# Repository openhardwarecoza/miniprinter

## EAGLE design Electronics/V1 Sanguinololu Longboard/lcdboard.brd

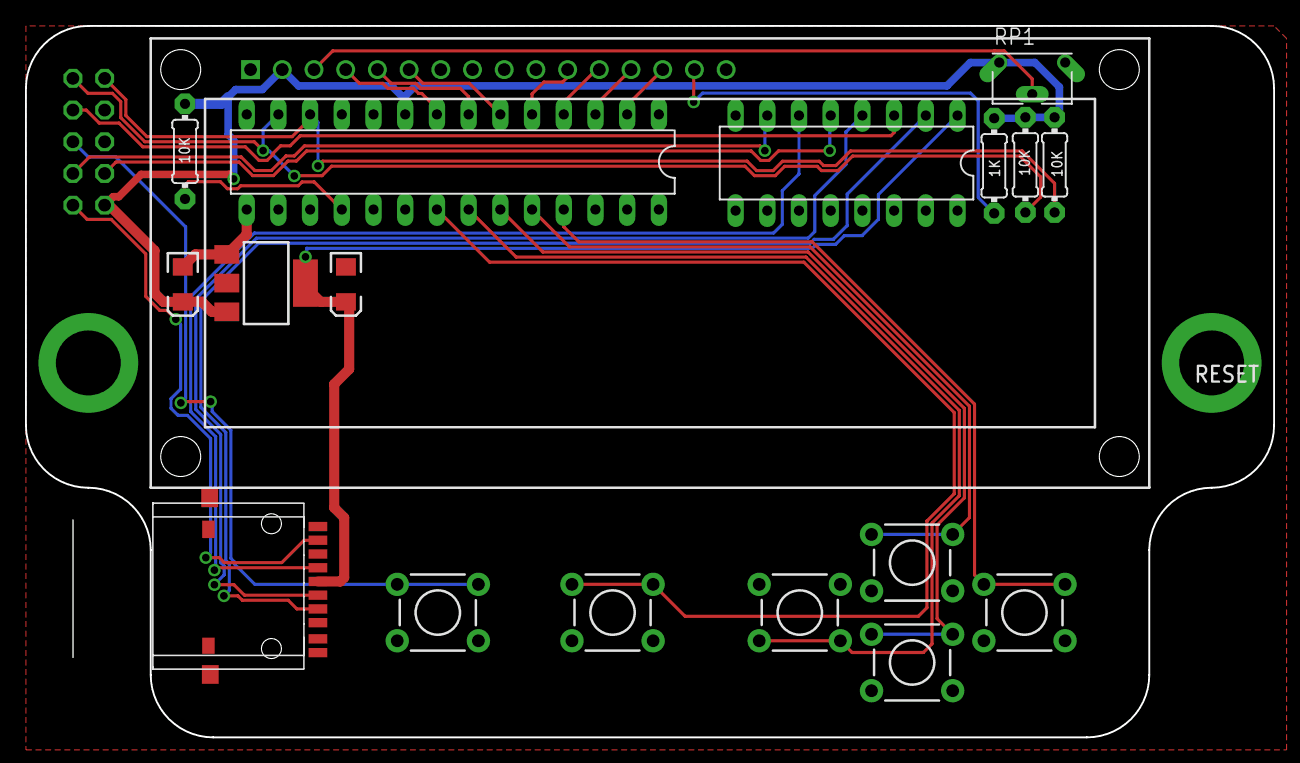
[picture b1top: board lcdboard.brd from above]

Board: 2 copper layers, 100.0 x 57.0 mm, 19 parts (1 on the bottom side), 28 nets.

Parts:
C2, C6: 10uF; EIA3216
IC1: MCP23017SP; DIL28-3
IC3: 1117-33; SOT223
IC5: 4050N; DIL16
JP1: 2X05
LCD16: LCD-HD447804-HOLES16X2-4-HOLES; LCD-16X2-4HOLES
R1, R2, R3, R6: 0204/7
RP1: BOURNS 3362-S-1-103LF; POT_B64W
S1, S2, S3, S4, S5, S6: RESET; TACTILE-PTH
U2: USD-SOCKETUSD; USD-SOCKET-PP

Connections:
3V3SD: C6.A, IC3.4, IC5.1, U2.4
5V: C2.A, IC1.9, IC3.3, JP1.2, LCD16.2, R1.1, R2.2, R3.2, R6.2, RP1.E
CS: IC5.2, U2.2
DB4: IC1.5, LCD16.11
DB5: IC1.4, LCD16.12
DB6: IC1.3, LCD16.13
DB7: IC1.2, LCD16.14
DI: IC5.4, U2.3
DO: JP1.1, U2.7
E: IC1.6, LCD16.6
GND: C2.C, C6.C, IC1.10, IC1.15, IC1.16, IC1.17, IC3.1, IC5.8, JP1.6, LCD16.1, LCD16.16, RP1.A, S1.3, S1.4, S2.3, S2.4, S3.3, S3.4, S4.3, S4.4, S5.3, S5.4, S6.3, S6.4, U2.6, U2.GND1, U2.GND2
MCURESET: JP1.5, S1.1, S1.2
MOSI: IC5.5, JP1.4
unnamed: LCD16.3, RP1.S
unnamed: LCD16.15, R6.1
P1: IC1.25, S2.1, S2.2
P2: IC1.24, S3.1, S3.2
P3: IC1.23, S4.1, S4.2
P4: IC1.22, S5.1, S5.2
P5: IC1.21, S6.1, S6.2
RESET: IC1.18, R3.1
RS: IC1.8, LCD16.4
RW: IC1.7, LCD16.5
SC: IC5.6, U2.5
SCK: IC5.7, JP1.3
SCL: IC1.12, JP1.10, R2.1
SDA: IC1.13, JP1.9, R1.2
SDS: IC5.3, JP1.7

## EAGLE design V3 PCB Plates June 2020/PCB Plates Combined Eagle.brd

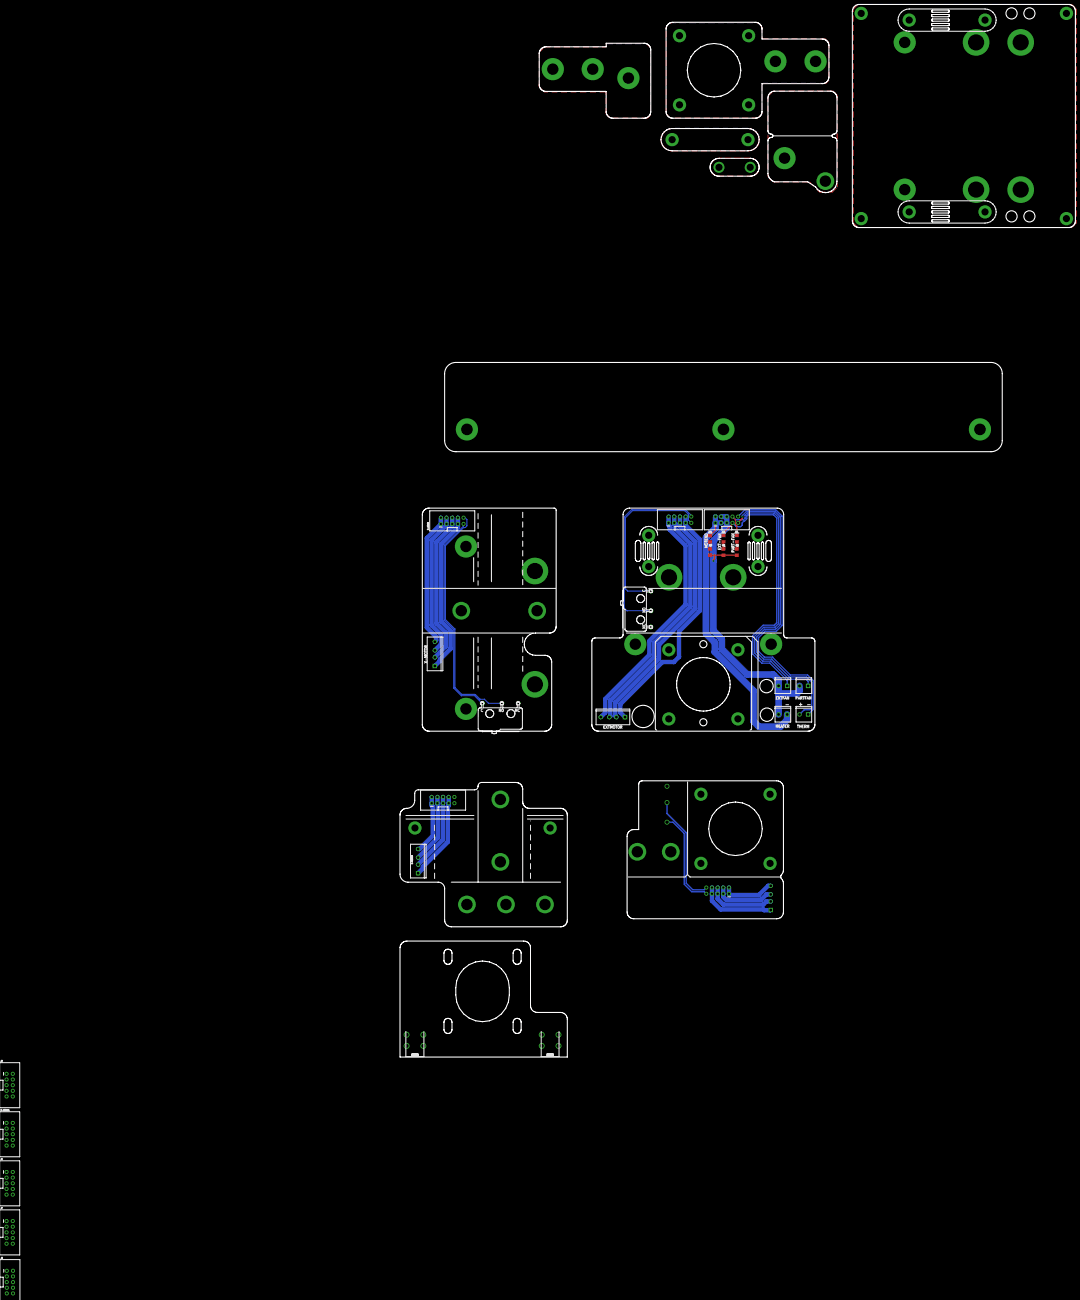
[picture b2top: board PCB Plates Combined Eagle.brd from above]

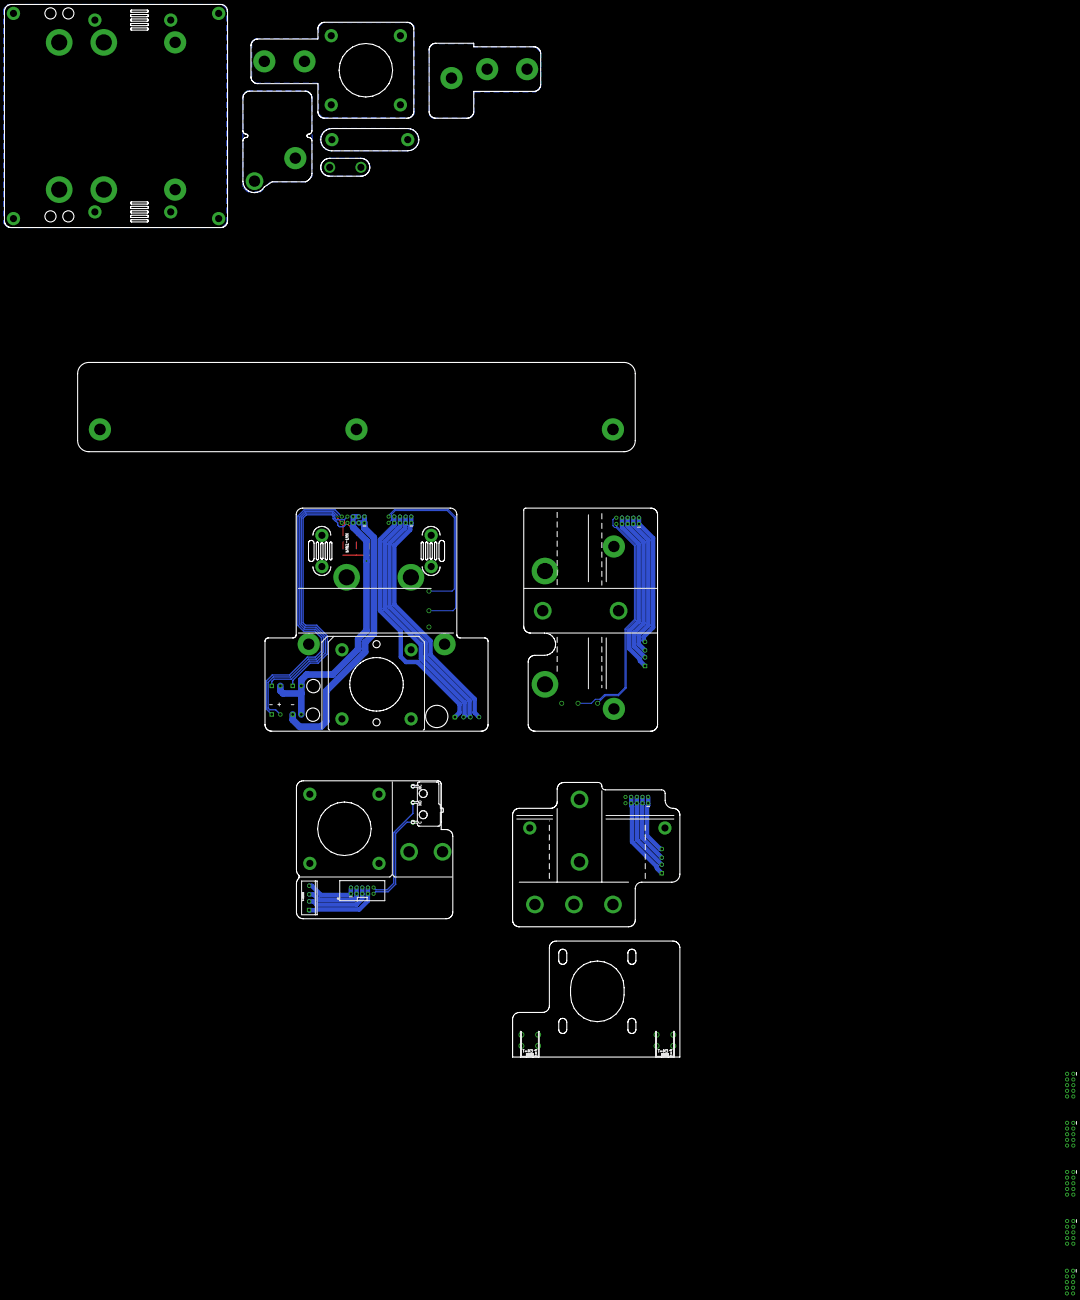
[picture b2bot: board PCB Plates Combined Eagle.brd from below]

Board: 2 copper layers, 302.8 x 471.9 mm, 29 parts (5 on the bottom side), 50 nets.

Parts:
CON1, CON7: PCB-2M3; PCB2-M3
D1, D2, D4: FKIT-LED-1206
EXTFAN: SCREWTERMINAL-3.5MM-2_LOCK
EXTMOTOR: SCREWTERMINAL-3.5MM-4_LOCK
HEATER: SCREWTERMINAL-3.5MM-2_LOCK
J1, J2, J3, J4, J5, J6, J7, J8: 2X5-SHROUDED_LOCK
PARTFAN: SCREWTERMINAL-3.5MM-2_LOCK
R1, R2, R3: R1206
THERM: SCREWTERMINAL-3.5MM-2_LOCK
U$1: Lever Microswitch Leftangle PCB mount, with Rolle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; LEVERMICROPCB-LEFTANGLE
X-MOTOR: SCREWTERMINAL-3.5MM-4_LOCK
XENDSTOP: Lever Microswitch Leftangle PCB mount, with Rolle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; LEVERMICROPCB-LEFTANGLE
Y-MOTOR: SCREWTERMINAL-3.5MM-4_LOCK
Z-CONN, Z-CONN1: 2X5-SHROUDED_LOCK
Z-MOTOR: SCREWTERMINAL-3.5MM-4_LOCK
ZENDSTOP: Lever Microswitch Leftangle PCB mount, with Rolle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; LEVERMICROPCB-LEFTANGLE

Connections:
24V: EXTFAN.2, HEATER.2, J4.4, J4.5, J4.6, PARTFAN.2, R1.2, R2.2, R3.2
24V1: J5.4, J5.5, J5.6
E-MOTOR-1: EXTMOTOR.1, J1.7, J1.8
E-MOTOR-2: EXTMOTOR.2, J1.5, J1.6
E-MOTOR-3: EXTMOTOR.3, J1.3, J1.4
E-MOTOR-4: EXTMOTOR.4, J1.1, J1.2
E-MOTOR-5: J7.1, J7.2
E-MOTOR-6: J7.3, J7.4
E-MOTOR-7: J7.5, J7.6
E-MOTOR-8: J7.7, J7.8
EXT-FAN-NEG: D2.C, EXTFAN.1, J4.7
HOTEND-NEG: D4.C, HEATER.1, J4.1, J4.2, J4.3
HOTEND-NEG1: J5.1, J5.2, J5.3
unnamed: D2.A, R1.1
unnamed: D1.A, R2.1
unnamed: D4.A, R3.1
PART-FAN-NEG: D1.C, J4.8, PARTFAN.1
THERM+: J4.10, THERM.1
THERM-: J4.9, THERM.2
X-END-C: J1.9, XENDSTOP.C
X-END-O: J1.10, XENDSTOP.NO
X-MOTOR-1: X-MOTOR.1, Z-CONN.7, Z-CONN.8
X-MOTOR-2: X-MOTOR.2, Z-CONN.5, Z-CONN.6
X-MOTOR-3: X-MOTOR.3, Z-CONN.3, Z-CONN.4
X-MOTOR-4: X-MOTOR.4, Z-CONN.1, Z-CONN.2
X-MOTOR-5: Z-CONN1.7, Z-CONN1.8
X-MOTOR-6: Z-CONN1.5, Z-CONN1.6
X-MOTOR-7: Z-CONN1.3, Z-CONN1.4
X-MOTOR-8: Z-CONN1.1, Z-CONN1.2
Y-ENDSTOP-C: J3.9, U$1.C
Y-ENDSTOP-NO: J3.10, U$1.NO
Y-MOTOR-1: J3.7, J3.8, Y-MOTOR.1
Y-MOTOR-2: J3.5, J3.6, Y-MOTOR.2
Y-MOTOR-3: J3.3, J3.4, Y-MOTOR.3
Y-MOTOR-4: J3.1, J3.2, Y-MOTOR.4
Y-MOTOR-5: J6.1, J6.2
Y-MOTOR-6: J6.3, J6.4
Y-MOTOR-7: J6.5, J6.6
Y-MOTOR-8: J6.7, J6.8
Z-ENDSTOP-C: Z-CONN.9, ZENDSTOP.C
Z-ENDSTOP-NO: Z-CONN.10, ZENDSTOP.NO
Z-MOTOR-1: J2.7, J2.8, Z-MOTOR.1
Z-MOTOR-2: J2.5, J2.6, Z-MOTOR.2
Z-MOTOR-3: J2.3, J2.4, Z-MOTOR.3
Z-MOTOR-4: J2.1, J2.2, Z-MOTOR.4
Z-MOTOR-5: J8.1, J8.2
Z-MOTOR-6: J8.3, J8.4
Z-MOTOR-7: J8.5, J8.6
Z-MOTOR-8: J8.7, J8.8
ZMOTORGND: CON1.P$1, CON1.P$2, CON1.P$3, CON1.P$4, CON7.P$1, CON7.P$2, CON7.P$3, CON7.P$4

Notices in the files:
parts and their libraries:
SparkFun-Connectors_PETERMICROSDEBAY: Licensing: CC v3.0 Share-Alike You are welcome to use this library for commercial purposes.
SparkFun-Connectors: Licensing: Creative Commons ShareAlike 4.0 International - https://creativecommons.org/licenses/by-sa/4.0
